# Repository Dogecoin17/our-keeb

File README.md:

# our-keeb
This is a hackclub organised program in which we built a fully custom keyboard ourselves. I decided to participate in this program, because I thought it would be a nice easy project, in which I can involve my gf,
and also learn some new skills. And I don't regret this decision! We had so much fun planning our keyboard, learning how to design pcbs in KiCAD and 3D models in Fusion. We managed to design so far a 60%-ish keyboard
with some custom buttons and a rotary encoder, and we're looking foward to bring it to life. At the end of the day I can proudly say, that thanks to this program we're going to make other fun projects together and 
I'm not doing this hobby alone anymore :)

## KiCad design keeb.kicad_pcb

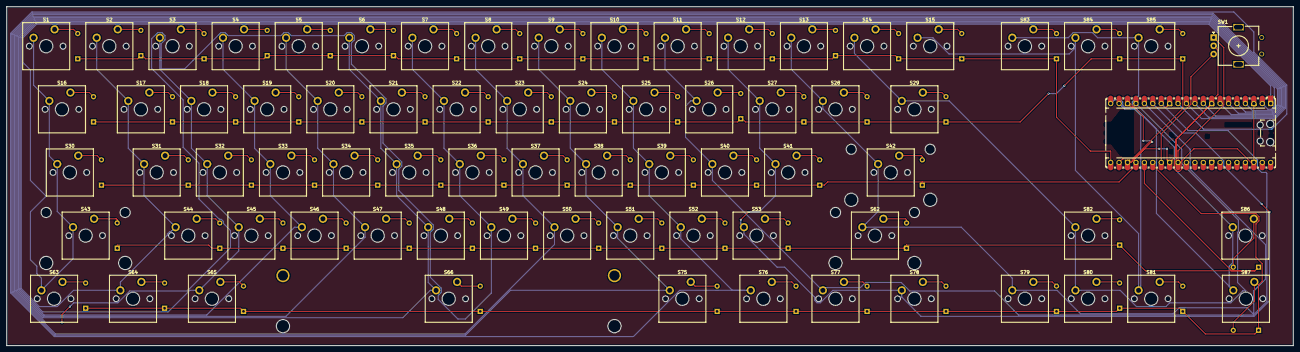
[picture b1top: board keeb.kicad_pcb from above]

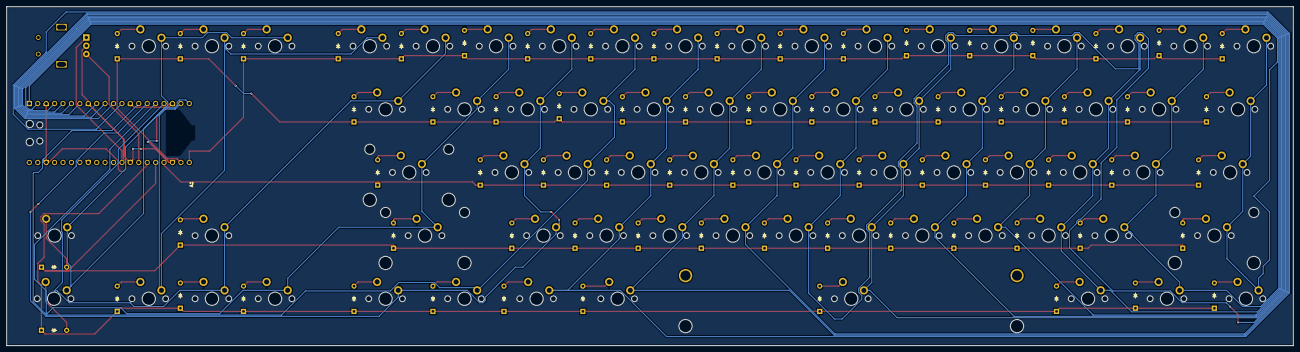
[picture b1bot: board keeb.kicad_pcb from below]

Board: 2 copper layers, 388.1 x 102.2 mm, 148 parts (71 on the bottom side), 95 nets.

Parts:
A1: RaspberryPi_Pico; RaspberryPi_Pico_Common_Unspecified
D1, D2, D3, D4, D5, D6, D7, D8, D9, D10, D11, D12, D13, D14, D15, D16, D17, D18, D19, D20, D21, D22, D23, D24, D25, D26, D27, D28, D29, D30, D31, D32, D33, D34, D35, D36, D37, D38, D39, D40, D41, D42, D43, D44, D45, D46, D47, D48, D49, D50, D51, D52, D53, D62, D63, D64, D65, D66, D75, D76, D77, D78, D79, D80, D81, D82, D83, D84, D85, D86, D87: Diode_DO-35
S1, S2, S3, S4, S5, S6, S7, S8, S9, S10, S11, S12, S13, S14, S15, S16, S17, S18, S19, S20, S21, S22, S23, S24, S25, S26, S27, S28, S29, S30, S31, S32, S33, S34, S35, S36, S37, S38, S39, S40, S41, S42, S43, S44, S45, S46, S47, S48, S49, S50, S51, S52, S53, S62, S63, S64, S65, S66, S75, S76, S77, S78, S79, S80, S81, S82, S83, S84, S85, S86, S87: MX_PCB_1.00u
S54: MX_stab; STAB_MX_P_6.25u
S55, S56: MX_stab; STAB_MX_2.25u
S57: MX_stab; STAB_MX_2.75u
SW1: RotaryEncoder; RotaryEncoder_Alps_EC11E_Vertical_H20mm

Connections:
unnamed: A1.3 (GND), A1.8 (GND), A1.13 (GND), A1.18 (GND), A1.23 (GND), A1.28 (GND), A1.38 (GND), SW1.C
unnamed: A1.27 (GPIO21), SW1.B
unnamed: A1.29 (GPIO22), SW1.A
unnamed: D1.2 (A), S1.2
unnamed: D2.2 (A), S2.2
unnamed: D3.2 (A), S3.2
unnamed: D4.2 (A), S4.2
unnamed: D5.2 (A), S5.2
unnamed: D6.2 (A), S6.2
unnamed: D7.2 (A), S7.2
unnamed: D8.2 (A), S8.2
unnamed: D9.2 (A), S9.2
unnamed: D10.2 (A), S10.2
unnamed: D11.2 (A), S11.2
unnamed: D12.2 (A), S12.2
unnamed: D13.2 (A), S13.2
unnamed: D14.2 (A), S14.2
unnamed: D15.2 (A), S15.2
unnamed: D16.2 (A), S16.2
unnamed: D17.2 (A), S17.2
unnamed: D18.2 (A), S18.2
unnamed: D19.2 (A), S19.2
unnamed: D20.2 (A), S20.2
unnamed: D21.2 (A), S21.2
unnamed: D22.2 (A), S22.2
unnamed: D23.2 (A), S23.2
unnamed: D24.2 (A), S24.2
unnamed: D25.2 (A), S25.2
unnamed: D26.2 (A), S26.2
unnamed: D27.2 (A), S27.2
unnamed: D28.2 (A), S28.2
unnamed: D29.2 (A), S29.2
unnamed: D30.2 (A), S30.2
unnamed: D31.2 (A), S31.2
unnamed: D32.2 (A), S32.2
unnamed: D33.2 (A), S33.2
unnamed: D34.2 (A), S34.2
unnamed: D35.2 (A), S35.2
unnamed: D36.2 (A), S36.2
unnamed: D37.2 (A), S37.2
unnamed: D38.2 (A), S38.2
unnamed: D39.2 (A), S39.2
unnamed: D40.2 (A), S40.2
unnamed: D41.2 (A), S41.2
unnamed: D42.2 (A), S42.2
unnamed: D43.2 (A), S43.2
unnamed: D44.2 (A), S44.2
unnamed: D45.2 (A), S45.2
unnamed: D46.2 (A), S46.2
unnamed: D47.2 (A), S47.2
unnamed: D48.2 (A), S48.2
unnamed: D49.2 (A), S49.2
unnamed: D50.2 (A), S50.2
unnamed: D51.2 (A), S51.2
unnamed: D52.2 (A), S52.2
unnamed: D53.2 (A), S53.2
unnamed: D62.2 (A), S62.2
unnamed: D63.2 (A), S63.2
unnamed: D64.2 (A), S64.2
unnamed: D65.2 (A), S65.2
unnamed: D66.2 (A), S66.2
unnamed: D75.2 (A), S75.2
unnamed: D76.2 (A), S76.2
unnamed: D77.2 (A), S77.2
unnamed: D78.2 (A), S78.2
unnamed: D79.2 (A), S79.2
unnamed: D80.2 (A), S80.2
unnamed: D81.2 (A), S81.2
unnamed: D82.2 (A), S82.2
unnamed: D83.2 (A), S83.2
unnamed: D84.2 (A), S84.2
unnamed: D85.2 (A), S85.2
unnamed: D86.2 (A), S86.2
unnamed: D87.2 (A), S87.2
col 0: A1.1 (GPIO0), S1.1, S16.1, S30.1, S43.1, S63.1
col 1: A1.2 (GPIO1), S2.1, S17.1, S31.1, S44.1, S64.1
col 2: A1.4 (GPIO2), S3.1, S18.1, S32.1, S45.1, S65.1
col 3: A1.5 (GPIO3), S4.1, S19.1, S33.1, S46.1
col 4: A1.6 (GPIO4), S5.1, S20.1, S34.1, S47.1
col 5: A1.7 (GPIO5), S6.1, S21.1, S35.1, S48.1, S66.1
col 6: A1.9 (GPIO6), S7.1, S22.1, S36.1, S49.1
col 7: A1.10 (GPIO7), S8.1, S23.1, S37.1, S50.1
col 8: A1.11 (GPIO8), S9.1, S24.1, S38.1, S51.1, S75.1
col 9: A1.12 (GPIO9), S10.1, S25.1, S39.1, S52.1, S76.1
col 10: A1.14 (GPIO10), S11.1, S26.1, S40.1, S77.1
col 11: A1.15 (GPIO11), S12.1, S27.1, S41.1, S53.1, S78.1
col 12: A1.16 (GPIO12), S13.1, S28.1, S42.1, S62.1, S79.1
col 13: A1.17 (GPIO13), S14.1, S29.1, S80.1, S82.1
col 14: A1.19 (GPIO14), S15.1, S81.1, S84.1
col 15: A1.20 (GPIO15), S83.1, S85.1, S86.1, S87.1
row 0: A1.21 (GPIO16), D1.1 (K), D2.1 (K), D3.1 (K), D4.1 (K), D5.1 (K), D6.1 (K), D7.1 (K), D8.1 (K), D9.1 (K), D10.1 (K), D11.1 (K), D12.1 (K), D13.1 (K), D14.1 (K), D15.1 (K), D83.1 (K)
row 1: A1.22 (GPIO17), D16.1 (K), D17.1 (K), D18.1 (K), D19.1 (K), D20.1 (K), D21.1 (K), D22.1 (K), D23.1 (K), D24.1 (K), D25.1 (K), D26.1 (K), D27.1 (K), D28.1 (K), D29.1 (K), D84.1 (K), D85.1 (K)
row 2: A1.24 (GPIO18), D30.1 (K), D31.1 (K), D32.1 (K), D33.1 (K), D34.1 (K), D35.1 (K), D36.1 (K), D37.1 (K), D38.1 (K), D39.1 (K), D40.1 (K), D41.1 (K), D42.1 (K)
row 3: A1.25 (GPIO19), D43.1 (K), D44.1 (K), D45.1 (K), D46.1 (K), D47.1 (K), D48.1 (K), D49.1 (K), D50.1 (K), D51.1 (K), D52.1 (K), D53.1 (K), D62.1 (K), D82.1 (K), D86.1 (K)
row 4: A1.26 (GPIO20), D63.1 (K), D64.1 (K), D65.1 (K), D66.1 (K), D75.1 (K), D76.1 (K), D77.1 (K), D78.1 (K), D79.1 (K), D80.1 (K), D81.1 (K), D87.1 (K)
